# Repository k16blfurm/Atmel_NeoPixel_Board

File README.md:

# Atmel_NeoPixel_Board

This is a first attempt at a Atmega328-AU board design. This board was designed in KiCad and I've given both schematics/layout. Here are some pictures. I've also added a usb mini b and 16 "NeoPixel" Leds in a string controlled by a singular pin. This was done in a day and I've followed EMC guidlines very loosely. I wouldn't base your design off of this lol.

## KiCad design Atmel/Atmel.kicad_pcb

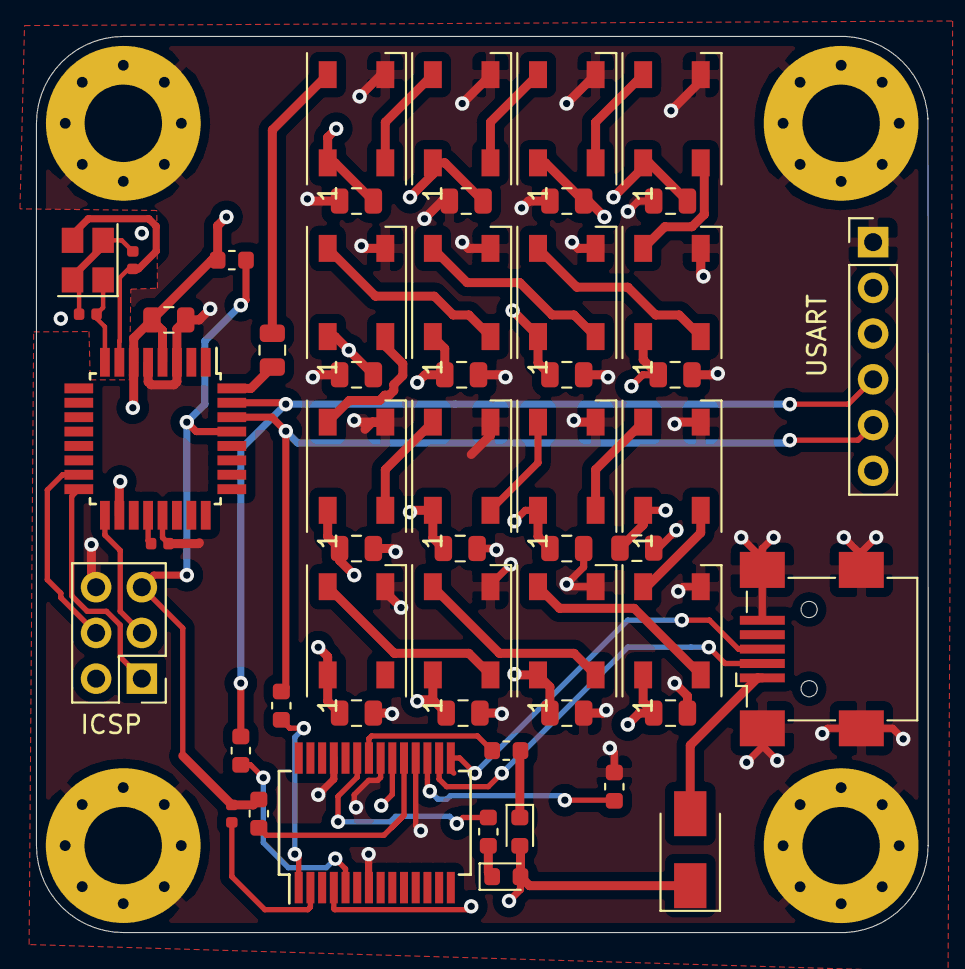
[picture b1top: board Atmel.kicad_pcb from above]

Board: 4 copper layers, 49.5 x 49.8 mm, 58 parts (0 on the bottom side), 41 nets.

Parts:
C1: 10u; C_0805_2012Metric
C2, C22: 0.1u; C_0402_1005Metric
C3, C4: 22p; C_0402_1005Metric
C5, C6, C7, C8, C9, C10, C11, C12, C13, C14, C15, C16, C17, C18, C19, C20: 0.1u; C_0805_2012Metric
C21, C23: 0.1u; C_0603_1608Metric
D1, D2, D3, D4, D5, D6, D7, D8, D9, D10, D11, D12, D13, D14, D15, D16: WS2812B; LED_WS2812B_PLCC4_5.0x5.0mm_P3.2mm
D17, D19: KT-0603R; LED_0603_1608Metric
D18: SS210; D_SMA
H1, H2, H3, H4: MountingHole_Pad; MountingHole_4.3mm_M4_Pad_Via
J1: Conn_02x03_Odd_Even; PinHeader_2x03_P2.54mm_Vertical
J2: Conn_01x06_Male; PinHeader_1x06_P2.54mm_Vertical
J3: USB_B_Mini; USB_Mini-B_Wuerth_65100516121_Horizontal
R1, R2, R3: 1k; R_0603_1608Metric
R4, R5: 330; R_0603_1608Metric
R6: 470; R_0805_2012Metric
U1: ATmega328-AU; TQFP-32_7x7mm_P0.8mm
U2: FT232RL; SSOP-28_5.3x10.2mm_P0.65mm
Y1: X322516MLB4SI; Crystal_SMD_3225-4Pin_3.2x2.5mm

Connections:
+5V: C1.2, C5.1, C6.1, C7.1, C8.1, C9.1, C10.1, C11.1, C12.1, C13.1, C14.1, C15.1, C16.1, C17.1, C18.1, C19.1, C20.1, D1.1, D2.1, D3.1, D4.1, D5.1, D6.1, D7.1, D8.1, D9.1, D10.1, D11.1, D12.1, D13.1, D14.1, D15.1, D16.1, D17.2, D18.1, D19.2, J1.2, J2.3, R1.1, U1.4, U1.6, U1.18, U2.4, U2.20
D2: D1.4, R6.1
GND: C1.1, C2.2, C5.2, C6.2, C7.2, C8.2, C9.2, C10.2, C11.2, C12.2, C13.2, C14.2, C15.2, C16.2, C17.2, C18.2, C19.2, C20.2, C21.2, D1.3, D2.3, D3.3, D4.3, D5.3, D6.3, D7.3, D8.3, D9.3, D10.3, D11.3, D12.3, D13.3, D14.3, D15.3, D16.3, H1.1, H2.1, H3.1, H4.1, J1.6, J2.1, J3.5, J3.6, U1.3, U1.5, U1.21, U2.7, U2.18, U2.21, U2.25
LED_ROW2: D4.2, D5.4
LED_ROW3: D8.2, D9.4
LED_ROW4: D12.2, D13.4
MISO: J1.1, U1.16
MOSI: J1.4, U1.15
unnamed: C2.1, U1.20
unnamed: C3.2, C4.2, Y1.2, Y1.4
unnamed: C21.1, U2.17
unnamed: C22.2, U2.2
unnamed: C23.1, U2.19
unnamed: D1.2, D2.4
unnamed: D2.2, D3.4
unnamed: D3.2, D4.4
unnamed: D5.2, D6.4
unnamed: D6.2, D7.4
unnamed: D7.2, D8.4
unnamed: D10.2, D11.4
unnamed: D9.2, D10.4
unnamed: D11.2, D12.4
unnamed: D13.2, D14.4
unnamed: D14.2, D15.4
unnamed: D15.2, D16.4
unnamed: D17.1, R4.1
unnamed: D19.1, R5.1
unnamed: J3.2, U2.16
unnamed: J3.3, U2.15
unnamed: R2.2, U2.1
unnamed: R3.2, U2.5
unnamed: R4.2, U2.23
unnamed: R5.2, U2.22
unnamed: R6.2, U1.32
RXD: J2.5, R2.1, U1.30
Reset: C22.1, C23.2, J1.5, R1.2, U1.29
SCK: J1.3, U1.17
TXD: J2.4, R3.1, U1.31
VUSB: D18.2, J3.1
XTAL1: C4.1, U1.7, Y1.3
XTAL2: C3.1, U1.8, Y1.1

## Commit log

2020-07-29 Initial Commit
    Initial Commit
2020-07-29 clean
    cleaning
